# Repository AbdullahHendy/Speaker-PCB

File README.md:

# Project Title

Class AB Amplifier Based Speakers With a Power Supply Circuit

## Description

A complete design of a 5W class AB audio amplifier with a power supply circuit and a speaker. 
The repository includes documentation for the design and fabrication files.

### Schematic

### Board Layout

### 3D View

## Dependencies

### Software

* The project was developed on Windows 10 using [KiCad 6.0](https://docs.kicad.org/6.0/)
* The libraries for the footprints and 3D models are included under the "KiCAD Libraries" directory. Might need to import them to the project.
* [Add symbol libraries to KiCad project](https://www.youtube.com/watch?v=iC3a5C4R820)
* [Add footprint libraries to KiCad project](https://www.youtube.com/watch?v=CBfGG5TKc6o)
* [Add 3D models to KiCad](https://www.youtube.com/watch?v=aqCzmXq5bb0)

### Hardware

* A 24V 1A power supply adapter is used to power up the speaker. A 24V 0.5A power supply adapter should also work with the possibility of lowering the performance 
	* [23V 1A Power Supply Adapter suggestion](https://www.amazon.com/gp/product/B09281KTS8/ref=ppx_yo_dt_b_asin_title_o02_s00?ie=UTF8&psc=1)

## Documentation
* Full Documentation can be found [here](https://github.com/AbdullahHendy/Speaker-PCB/tree/main/Documentation)
	* [Report](https://github.com/AbdullahHendy/Speaker-PCB/blob/main/Documentation/Amplifier%20Project%20Report.pdf) explaining all design details and why most of design decisions were made
    * See this [important fixes and imporovements for later versions](https://github.com/AbdullahHendy/Speaker-PCB/blob/main/Documentation/Fixes_Improvements.pdf)
    
## Authors

Contributors names and contact info

[@AbdullahHendy](https://www.linkedin.com/in/abdullah-hendy/)

## Version History

* 00
    * Initial version

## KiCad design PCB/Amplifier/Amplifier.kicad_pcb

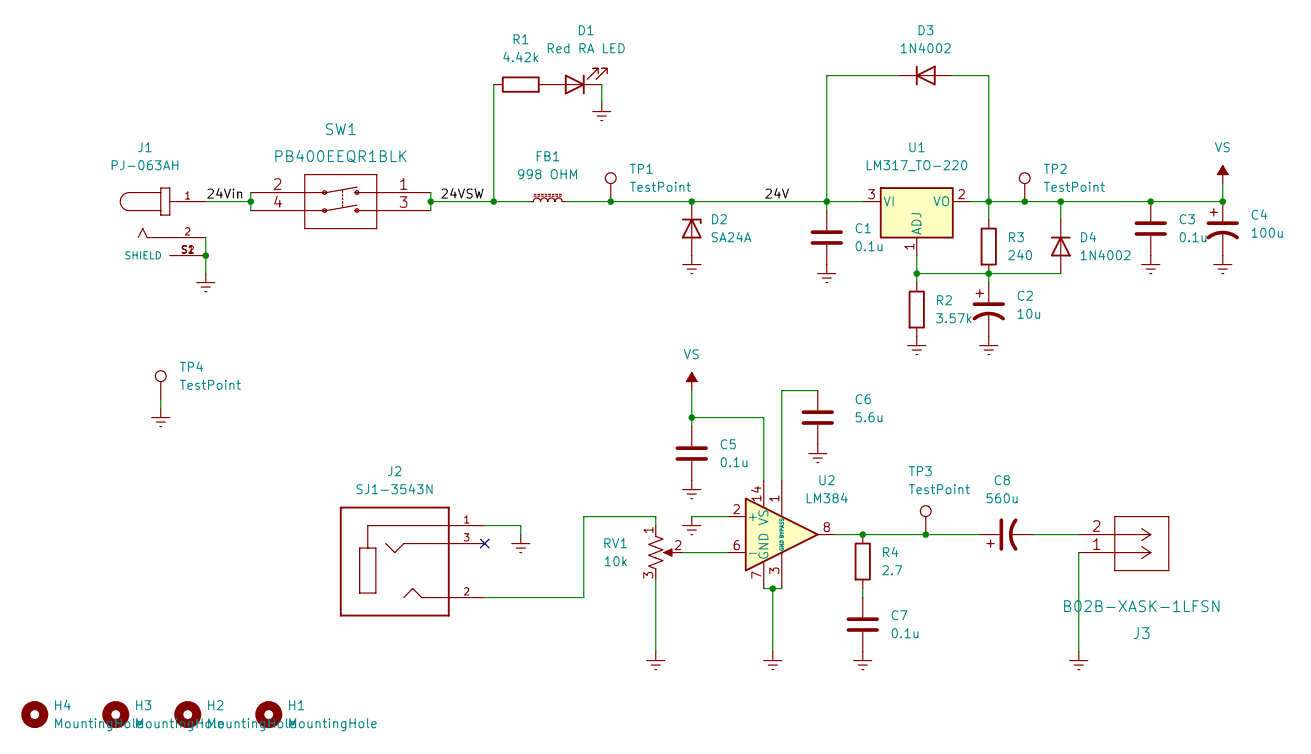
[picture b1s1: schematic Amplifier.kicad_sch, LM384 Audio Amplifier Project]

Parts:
C1, C3, C5, C7: 0.1u; C_Rect_L4.0mm_W2.5mm_P2.50mm
C2: 10u; CP_Radial_D5.0mm_P2.00mm
C4: 100u; CP_Radial_D6.3mm_P2.50mm
C6: 5.6u; CP_Radial_D5.0mm_P2.00mm
C8: 560u; CP_Radial_D10.0mm_P5.00mm
D1: Red RA LED; LED_D3.0mm_Horizontal_O1.27mm_Z6.0mm
D2: SA24A; D_DO-15_P12.70mm_Horizontal
D3, D4: 1N4002; D_DO-41_SOD81_P10.16mm_Horizontal
FB1: 998 OHM; FB_28C0236-0EW-10
H1, H2, H3, H4: MountingHole; MountingHole_3.2mm_M3_Pad
J1: PJ-063AH; CUI_PJ-063AH; PARTREV 1.02
J2: SJ1-3543N; CUI_SJ1-3543N; PARTREV 1.01
J3: B02B-XASK-1LFSN
R1: 4.42k; R_Axial_DIN0207_L6.3mm_D2.5mm_P10.16mm_Horizontal
R2: 3.57k; R_Axial_DIN0207_L6.3mm_D2.5mm_P10.16mm_Horizontal
R3: 240; R_Axial_DIN0207_L6.3mm_D2.5mm_P10.16mm_Horizontal
R4: 2.7; R_Axial_DIN0207_L6.3mm_D2.5mm_P10.16mm_Horizontal
RV1: 10k; PTV09A2020FA104
SW1: PB400EEQR1BLK
TP1, TP2, TP3, TP4: TestPoint; TestPoint_Keystone_5000-5004_Miniature_01
U1: LM317_TO-220; TO-220-3_Vertical
U2: LM384; DIP-14_W7.62mm

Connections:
/24V: C1.1, D2.1 (K), D3.1 (K), FB1.2, TP1.1, U1.3 (VI)
/24VSW: FB1.1, R1.1, SW1.1, SW1.3
/24Vin: J1.1, SW1.2, SW1.4
GNDREF: C1.2, C2.2, C3.2, C4.2, C5.2, C6.2, C7.2, D1.1 (K), D2.2 (A), H1.1, H2.1, H3.1, H4.1, J1.2, J1.S1 (SHIELD), J1.S2 (SHIELD), J2.1, J3.1, R2.2, RV1.3, TP4.1, U2.2 (+), U2.3 (GND), U2.4 (GND), U2.5 (GND), U2.7 (GND), U2.10 (GND), U2.11 (GND), U2.12 (GND)
unnamed: C2.1, D4.2 (A), R2.1, R3.2, U1.1 (ADJ)
unnamed: C6.1, U2.1 (BYPASS)
unnamed: C7.1, R4.2
unnamed: C8.1, R4.1, TP3.1, U2.8
unnamed: C8.2, J3.2
unnamed: D1.2 (A), R1.2
unnamed: J2.2, RV1.1
unnamed: RV1.2, U2.6 (-)
VS: C3.1, C4.1, C5.1, D3.2 (A), D4.1 (K), R3.1, TP2.1, U1.2 (VO), U2.14 (VS)

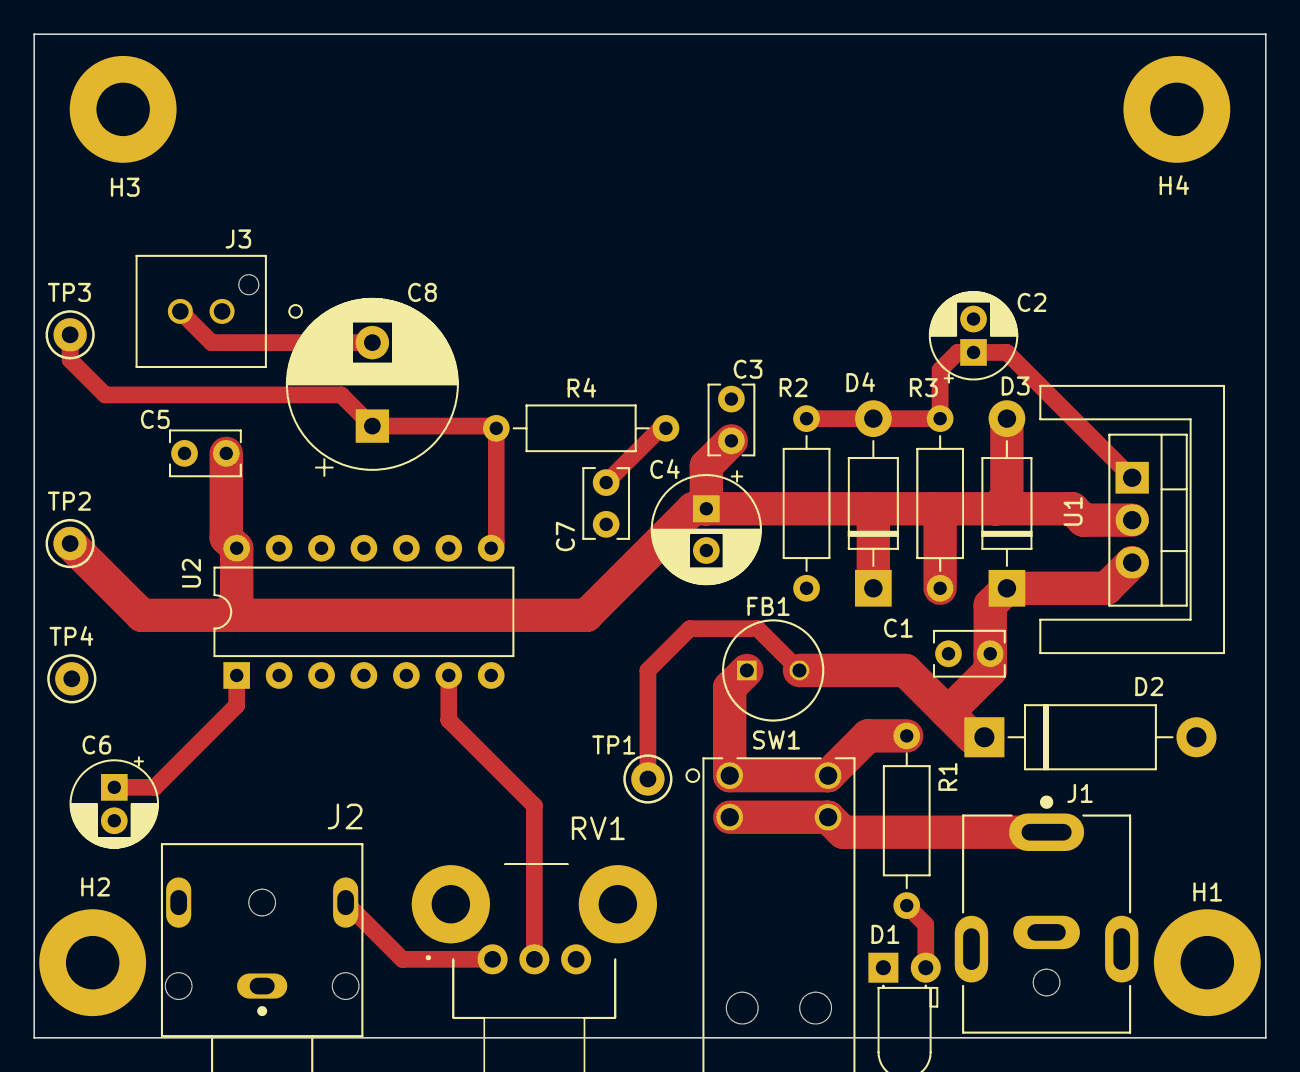
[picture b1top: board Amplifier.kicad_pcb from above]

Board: 2 copper layers, 73.8 x 60.1 mm, 32 parts (0 on the bottom side), 13 nets.

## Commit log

2023-08-18 published the project
2023-08-18 added schematic, layout, and 3D model of the project
2023-08-18 added read me
2023-08-19 updated read me and the documentation
2023-08-20 updated the final report for the project, updated the fixes and improvements files, and replaced docx files with pdf ones
2023-08-20 updated documentation format
2023-08-27 update documentation format
2024-07-28 updated links in README
2025-12-14 Updated Docs including .docx files

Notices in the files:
parts and their libraries:
Copyright 2021 Accelerated Designs. All rights reserved.
